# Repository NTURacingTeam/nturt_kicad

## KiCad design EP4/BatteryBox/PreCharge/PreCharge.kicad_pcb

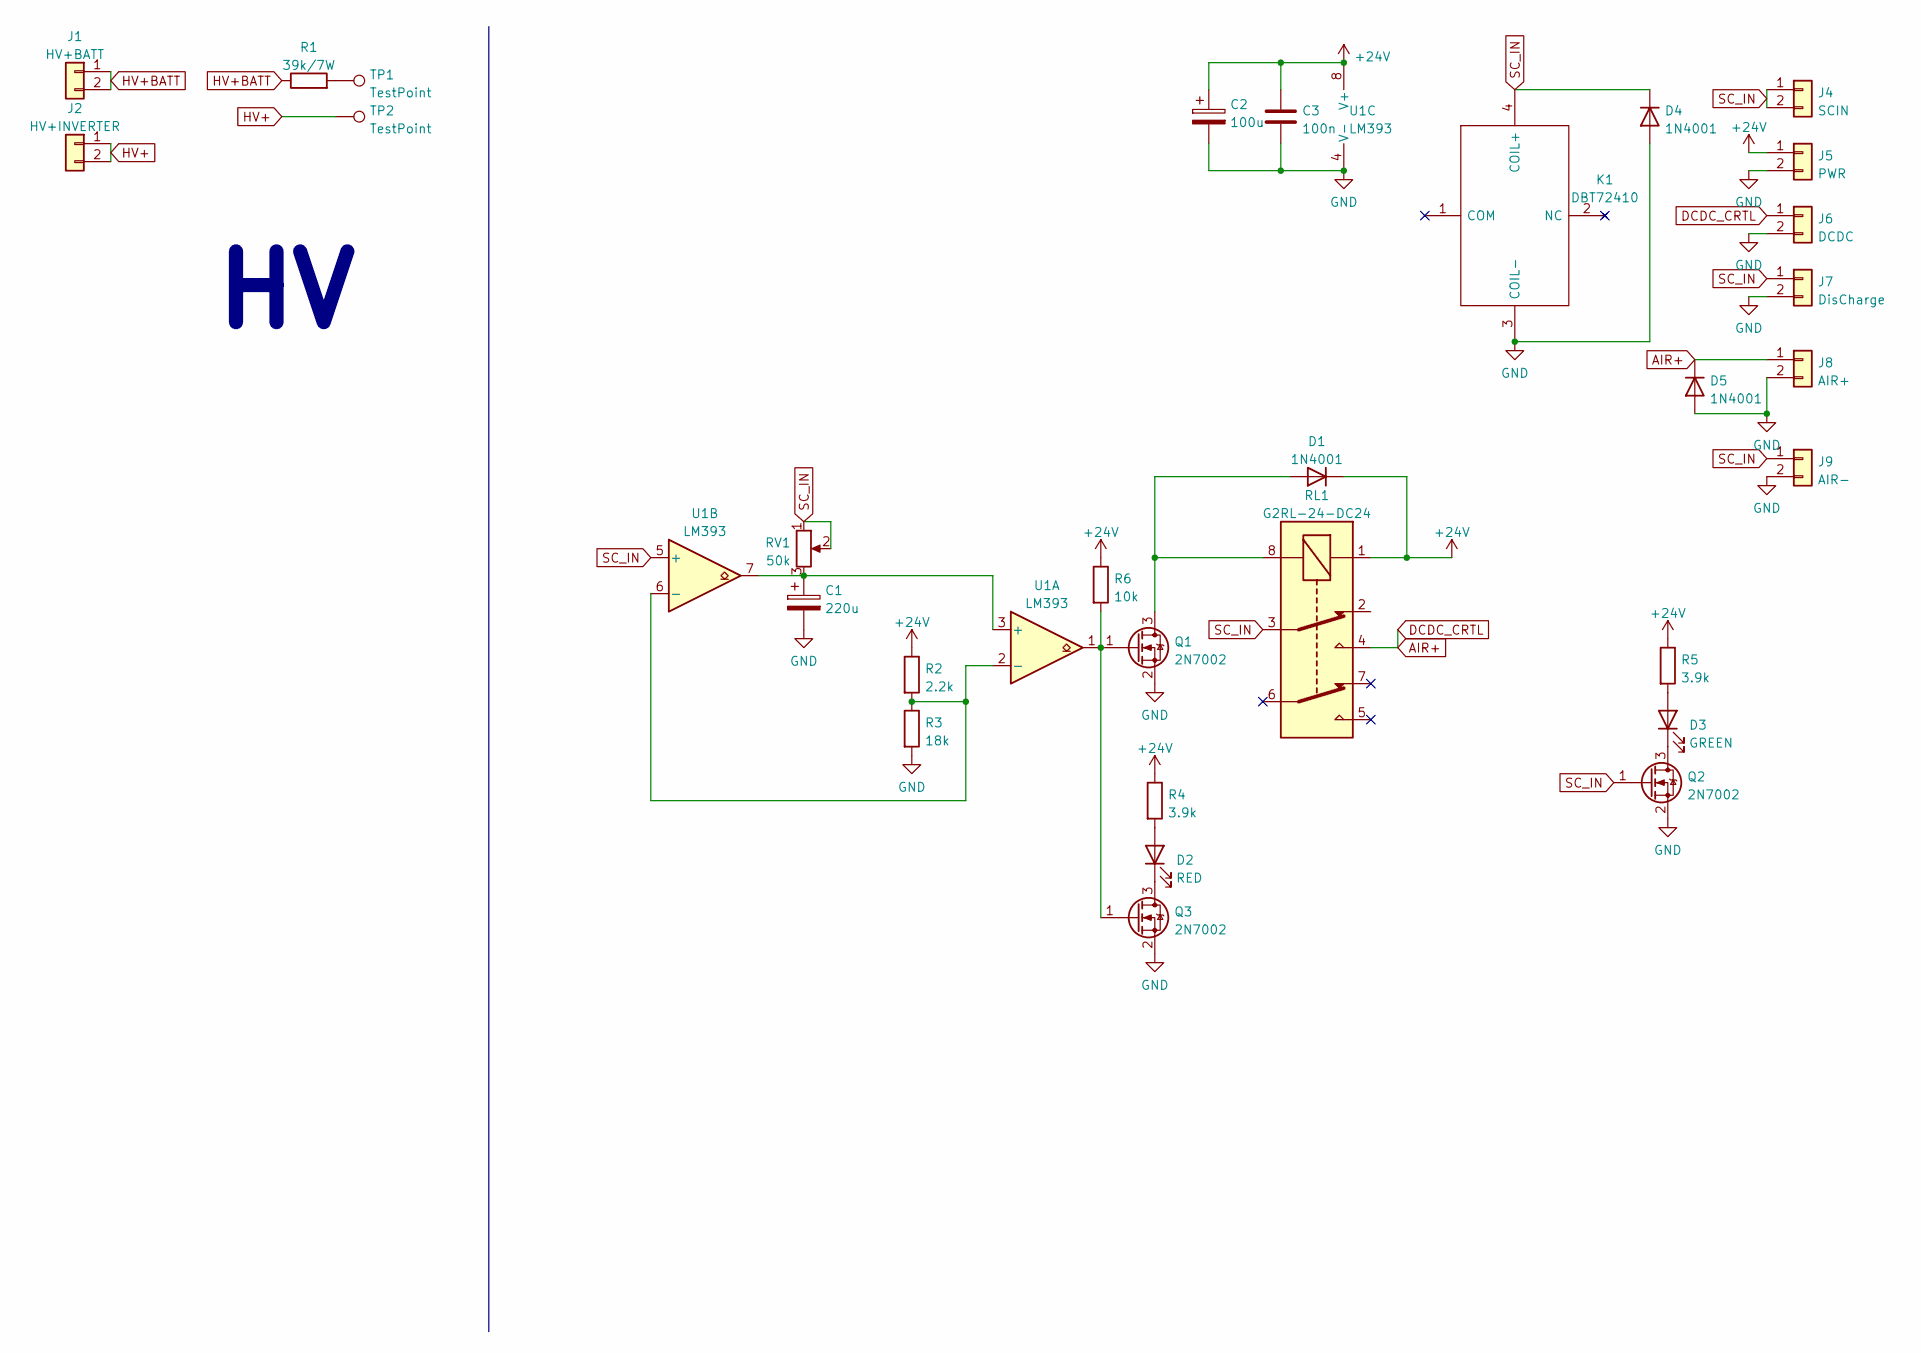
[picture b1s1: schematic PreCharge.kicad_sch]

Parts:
C1: 220u; CP_Elec_10x10
C2: 100u; CP_Elec_10x10
C3: 100n; C_0805_2012Metric_Pad1.18x1.45mm_HandSolder
D1, D4, D5: 1N4001; D_DO-41_SOD81_P10.16mm_Horizontal
D2: RED; LED_0805_2012Metric_Pad1.15x1.40mm_HandSolder
D3: GREEN; LED_0805_2012Metric_Pad1.15x1.40mm_HandSolder
J1: HV+BATT; DF33C2P33DSA24
J2: HV+INVERTER; DF33C2P33DSA24
J4: SCIN; DF33C2P33DSA24
J5: PWR; DF33C2P33DSA24
J6: DCDC; DF33C2P33DSA24
J7: DisCharge; DF33C2P33DSA24
J8: AIR+; DF33C2P33DSA24
J9: AIR-; DF33C2P33DSA24
K1: DBT72410; Manufacturer_Part_Number DBT72410
Q1, Q2, Q3: 2N7002; SOT-23
R1: 39k/7W; RESM24595X990N
R2: 2.2k; R_0805_2012Metric_Pad1.20x1.40mm_HandSolder
R3: 18k; R_0805_2012Metric_Pad1.20x1.40mm_HandSolder
R4, R5: 3.9k; R_0805_2012Metric_Pad1.20x1.40mm_HandSolder
R6: 10k; R_0805_2012Metric_Pad1.20x1.40mm_HandSolder
RL1: G2RL-24-DC24; Relay_DPDT_Omron_G2RL
RV1: 50k; Potentiometer_Bourns_3386P_Vertical
TP1, TP2: TestPoint; TestPoint_Loop_D2.50mm_Drill1.85mm
U1: LM393; SOIC-8_3.9x4.9mm_P1.27mm

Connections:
+24V: C2.1, C3.1, D1.1 (K), J5.1, R2.1, R4.1, R5.1, R6.1, RL1.1, U1.8 (V+)
AIR+: D5.1 (K), J6.1, J8.1, RL1.4
GND: C1.2, C2.2, C3.2, D4.2 (A), D5.2 (A), J5.2, J6.2, J7.2, J8.2, J9.2, K1.3 (COIL-), Q1.2 (S), Q2.2 (S), Q3.2 (S), R3.2, U1.4 (V-)
HV+: J2.1, J2.2, TP2.1
HV+BATT: J1.1, J1.2, R1.1
unnamed: D1.2 (A), Q1.3 (D), RL1.8
unnamed: D2.1 (K), Q3.3 (D)
unnamed: D2.2 (A), R4.2
unnamed: D3.1 (K), Q2.3 (D)
unnamed: D3.2 (A), R5.2
unnamed: Q1.1 (G), Q3.1 (G), R6.2, U1.1
unnamed: R1.2, TP1.1
unnamed: R2.2, R3.1, U1.2 (-), U1.6 (-)
unnamed: C1.1, RV1.3, U1.3 (+), U1.7
SC_IN: D4.1 (K), J4.1, J4.2, J7.1, J9.1, K1.4 (COIL+), Q2.1 (G), RL1.3, RV1.1, RV1.2, U1.5 (+)

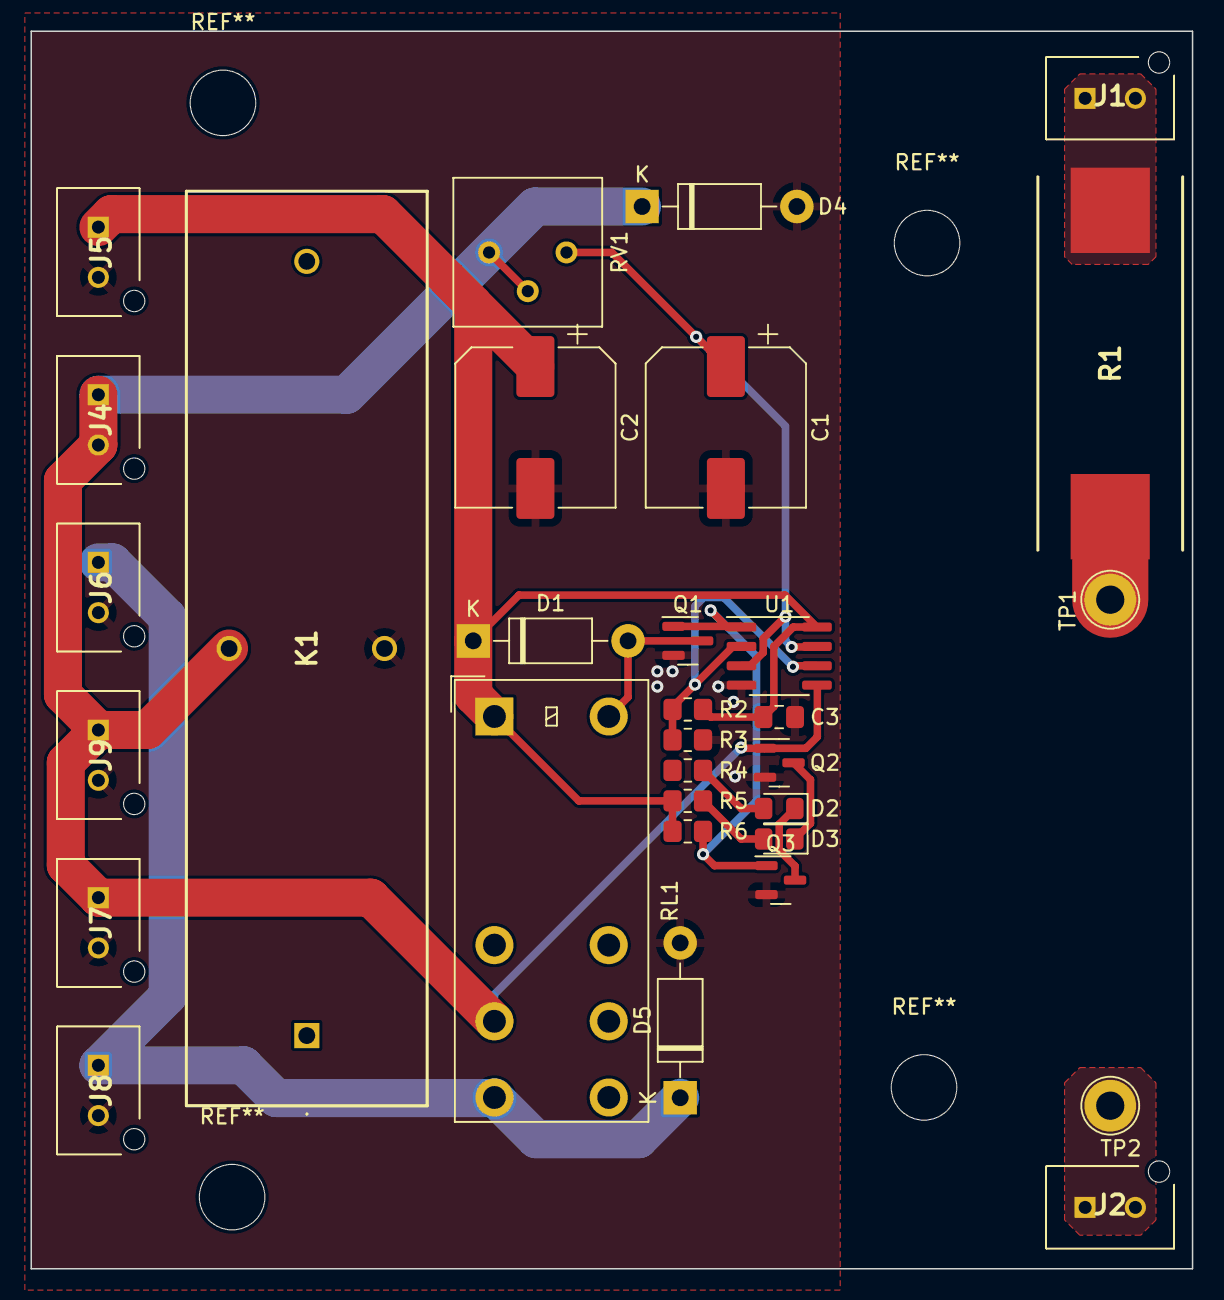
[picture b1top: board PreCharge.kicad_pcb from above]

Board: 2 copper layers, 76.2 x 81.2 mm, 31 parts (0 on the bottom side), 15 nets.

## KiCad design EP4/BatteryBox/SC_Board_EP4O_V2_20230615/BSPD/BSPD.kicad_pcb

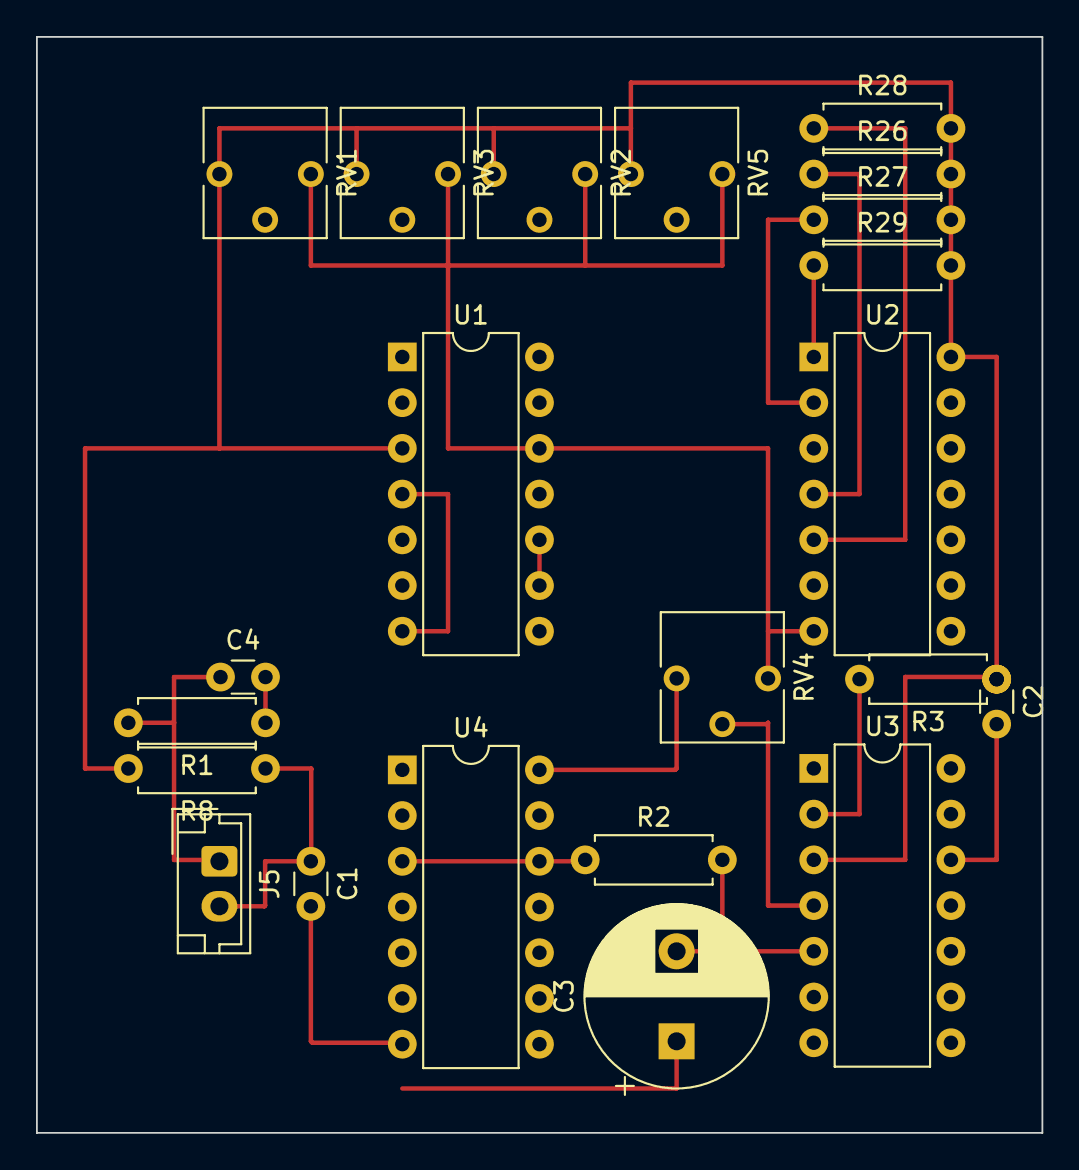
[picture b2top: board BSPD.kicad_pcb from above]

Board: 4 copper layers, 55.9 x 60.9 mm, 22 parts (0 on the bottom side), 18 nets.

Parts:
C1, C2, C4: 0.1uF; C_Disc_D3.0mm_W1.6mm_P2.50mm
C3: 100uF; CP_Radial_D10.0mm_P5.00mm
J5: BSPD I/O; JST_EH_B2B-EH-A_1x02_P2.50mm_Vertical
R1, R8, R26, R27, R28, R29: 1k; R_Axial_DIN0207_L6.3mm_D2.5mm_P7.62mm_Horizontal
R2: 5.1k; R_Axial_DIN0207_L6.3mm_D2.5mm_P7.62mm_Horizontal
R3: 39k; R_Axial_DIN0207_L6.3mm_D2.5mm_P7.62mm_Horizontal
RV1, RV2, RV3, RV4, RV5: R_POT; Potentiometer_Vishay_T73YP_Vertical
U1, U3: LM339; DIP-14_W7.62mm
U2: 74LS32; DIP-14_W7.62mm
U4: 74LS08; DIP-14_W7.62mm

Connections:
+5V: C2.1, R3.1, R8.2, R26.2, R27.2, R28.2, R29.2, RV1.1, RV2.1, RV3.1, RV4.1, RV5.1, U1.3 (V+), U2.14 (VCC), U3.3 (V+), U4.14 (VCC)
BPD_fault: R3.2, U3.2
GND: C1.2, C2.2, C3.1, C4.2, R1.1, RV1.3, RV2.3, RV3.3, RV4.3, RV5.3, U1.12 (V-), U2.7 (GND), U3.12 (V-), U4.7 (GND)
unnamed: C1.1, J5.2, R8.1, U1.4 (-), U1.7 (+)
unnamed: C3.2, R2.2, U3.5 (+)
unnamed: C4.1, J5.1, R1.2, U1.9 (+), U1.10 (-)
unnamed: R26.1, U1.13, U2.4
unnamed: R27.1, U1.1, U2.2
unnamed: R28.1, U1.14, U2.5
unnamed: R29.1, U1.2, U2.1
unnamed: RV1.2, U1.5 (+)
unnamed: RV2.2, U1.11 (+)
unnamed: RV3.2, U1.6 (-)
unnamed: RV4.2, U3.4 (-)
unnamed: RV5.2, U1.8 (-)
unnamed: U2.3, U4.1
unnamed: U2.6, U4.2
unnamed: R2.1, U4.3, U4.12

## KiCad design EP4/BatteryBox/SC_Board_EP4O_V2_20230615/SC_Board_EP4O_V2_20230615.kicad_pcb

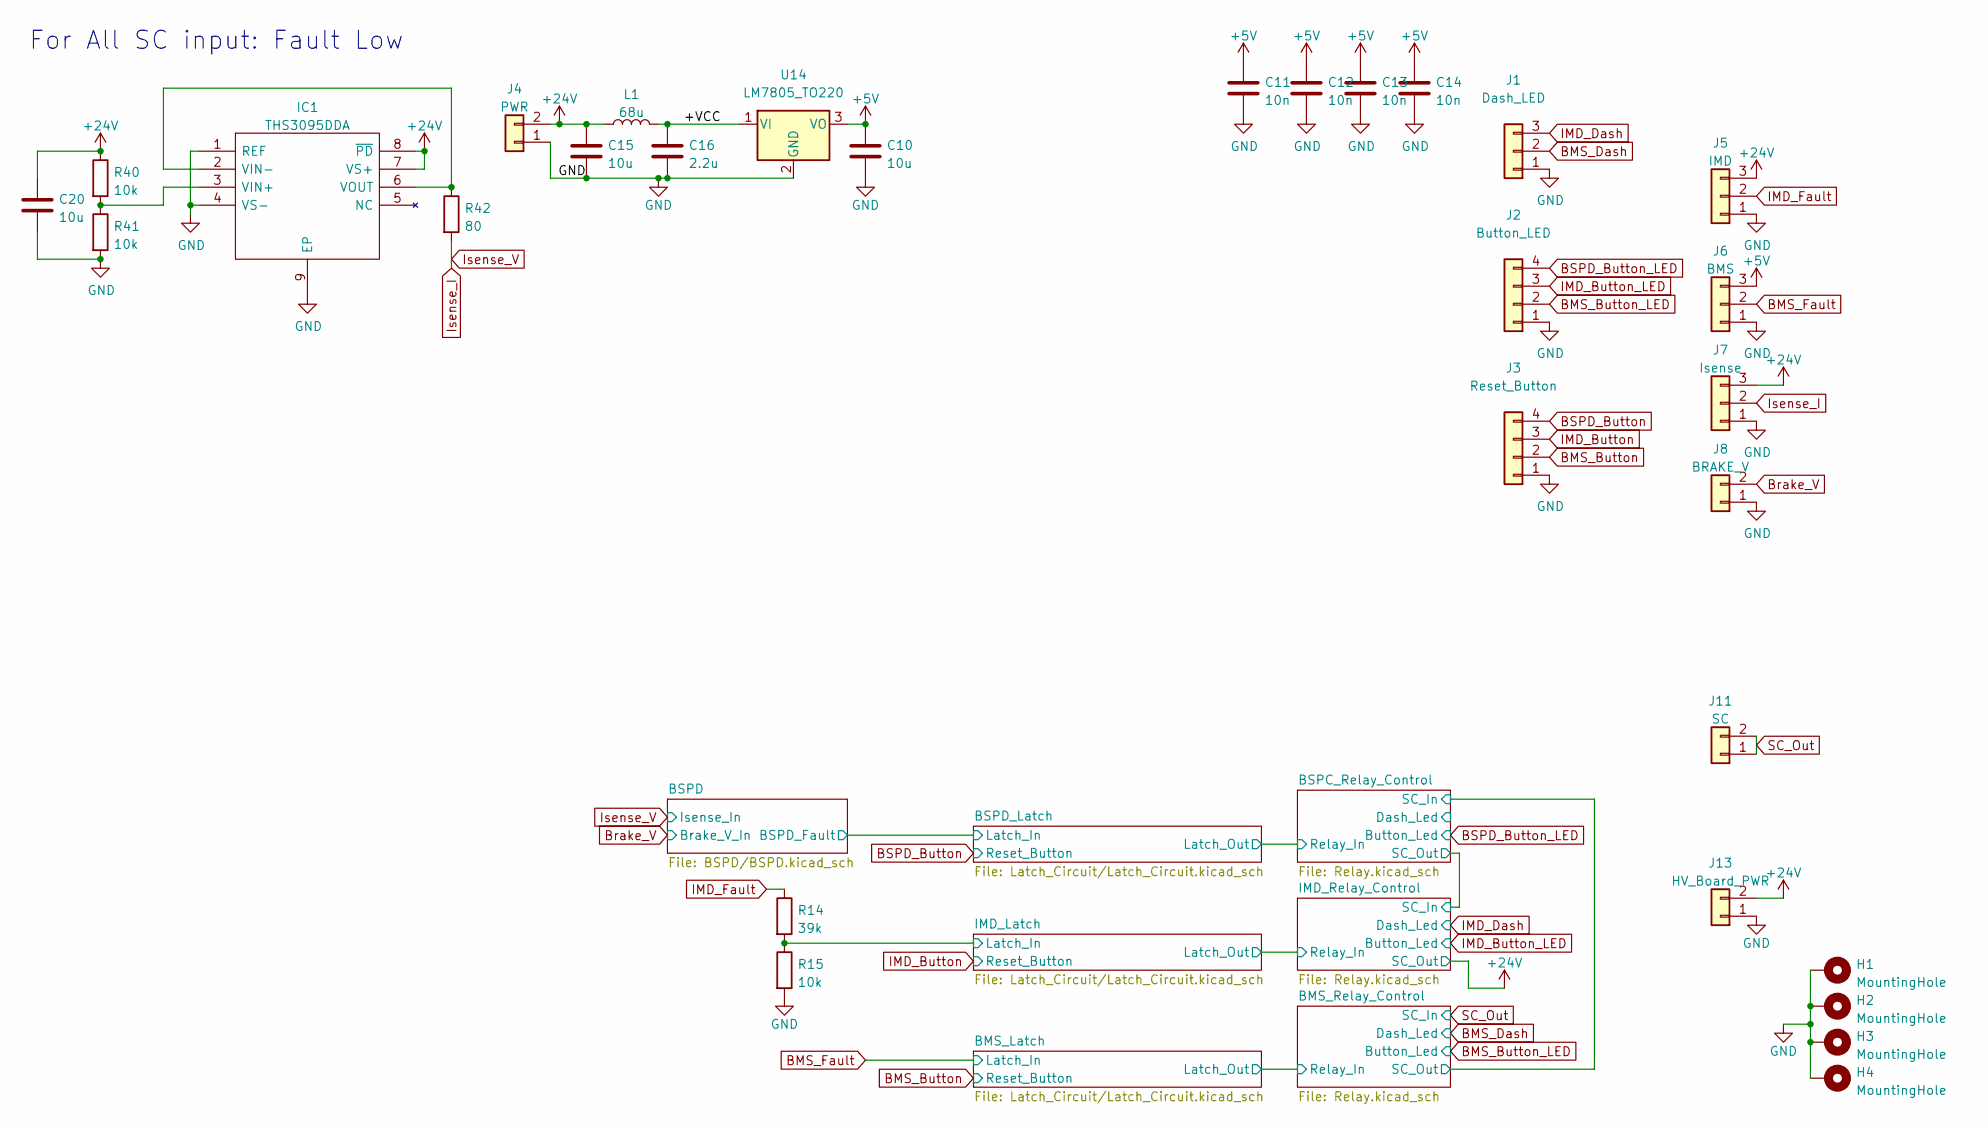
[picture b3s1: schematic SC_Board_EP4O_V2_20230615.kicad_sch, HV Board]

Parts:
C10, C15, C20: 10u; C_1206_3216Metric_Pad1.33x1.80mm_HandSolder
C11, C12, C13, C14: 10n; C_0805_2012Metric_Pad1.18x1.45mm_HandSolder
C16: 2.2u; C_1206_3216Metric_Pad1.33x1.80mm_HandSolder
H1, H2, H3, H4: MountingHole; MountingHole_4.3mm_M4_Pad_Via
IC1: THS3095DDA; SOIC127P600X170-9N; Mouser Part Number 595-THS3095DDA
J1: Dash_LED; JST_PH_B3B-PH-K_1x03_P2.00mm_Vertical
J2: Button_LED; JST_PH_B4B-PH-K_1x04_P2.00mm_Vertical
J3: Reset_Button; JST_PH_B4B-PH-K_1x04_P2.00mm_Vertical
J4: PWR; JST_PH_B2B-PH-K_1x02_P2.00mm_Vertical
J5: IMD; JST_PH_B3B-PH-K_1x03_P2.00mm_Vertical
J6: BMS; JST_PH_B3B-PH-K_1x03_P2.00mm_Vertical
J7: Isense; JST_PH_B3B-PH-K_1x03_P2.00mm_Vertical
J8: BRAKE_V; JST_PH_B2B-PH-K_1x02_P2.00mm_Vertical
J11: SC; JST_PH_B2B-PH-K_1x02_P2.00mm_Vertical
J13: HV_Board_PWR; JST_PH_B2B-PH-K_1x02_P2.00mm_Vertical
L1: 68u; RLS686
R14: 39k; R_0805_2012Metric_Pad1.20x1.40mm_HandSolder
R15, R40, R41: 10k; R_0805_2012Metric_Pad1.20x1.40mm_HandSolder
R42: 80; R_Axial_Power_L38.0mm_W6.4mm_P40.64mm
U14: LM7805_TO220; TO-220-3_Vertical

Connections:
+5V: C10.1, C11.1, C12.1, C13.1, C14.1, J6.3, U14.3 (VO); also elsewhere on the board
+24V: C15.1, C20.1, IC1.7 (VS+), IC1.8 (~PD), J4.2, J5.3, J7.3, J13.2, L1.1, R40.1; also elsewhere on the board
/+VCC: C16.1, L1.2, U14.1 (VI)
/IMD_Latch/Latch_In: R14.2, R15.1; also elsewhere on the board
BMS_Button: J3.2; also elsewhere on the board
BMS_Button_LED: J2.2; also elsewhere on the board
BMS_Dash: J1.2; also elsewhere on the board
BMS_Fault: J6.2; also elsewhere on the board
BSPD_Button: J3.4; also elsewhere on the board
BSPD_Button_LED: J2.4; also elsewhere on the board
Brake_V: J8.2; also elsewhere on the board
GND: C10.2, C11.2, C12.2, C13.2, C14.2, C15.2, C16.2, C20.2, H1.1, H2.1, H3.1, H4.1, IC1.1 (REF), IC1.4 (VS-), IC1.9 (EP), J1.1, J2.1, J3.1, J4.1, J5.1, J6.1, J7.1, J8.1, J13.1, R15.2, R41.2, U14.2 (GND); also elsewhere on the board
IMD_Button: J3.3; also elsewhere on the board
IMD_Button_LED: J2.3; also elsewhere on the board
IMD_Dash: J1.3; also elsewhere on the board
IMD_Fault: J5.2, R14.1
Isense_I: J7.2, R42.2; also elsewhere on the board
unnamed: IC1.2 (VIN-), IC1.6 (VOUT), R42.1
unnamed: IC1.3 (VIN+), R40.2, R41.1
SC_Out: J11.1, J11.2; also elsewhere on the board

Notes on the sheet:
For All SC input: Fault Low

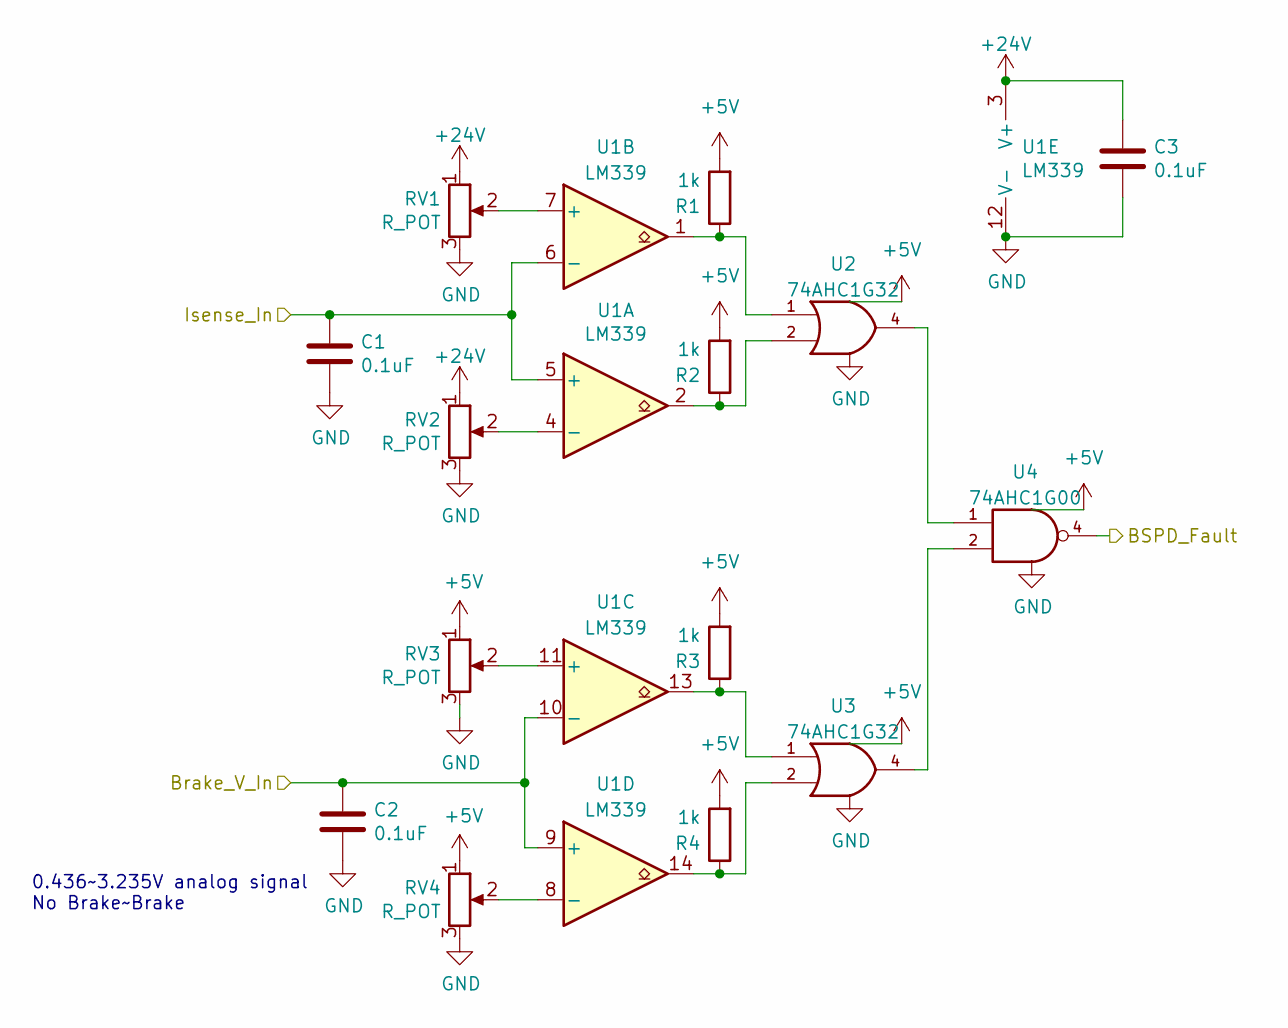
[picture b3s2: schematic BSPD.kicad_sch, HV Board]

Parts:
C1, C2, C3: 0.1uF; C_0805_2012Metric_Pad1.18x1.45mm_HandSolder
R1, R2, R3, R4: 1k; R_0805_2012Metric_Pad1.20x1.40mm_HandSolder
RV1, RV2, RV3, RV4: R_POT; Potentiometer_Bourns_3296P_Horizontal
U1: LM339; SOIC-14_3.9x8.7mm_P1.27mm
U2, U3: 74AHC1G32; SOT-23-5_HandSoldering
U4: 74AHC1G00; SOT-23-5_HandSoldering

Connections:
+5V: R1.2, R2.2, R3.2, R4.2, RV3.1, RV4.1, U2.5 (VCC), U3.5 (VCC), U4.5 (VCC); also elsewhere on the board
+24V: C3.1, RV1.1, RV2.1, U1.3 (V+); also elsewhere on the board
/BSPD/BSPD_Fault: U4.4; also elsewhere on the board
Brake_V: C2.1, U1.9 (+), U1.10 (-); also elsewhere on the board
GND: C1.2, C2.2, C3.2, RV1.3, RV2.3, RV3.3, RV4.3, U1.12 (V-), U2.3 (GND), U3.3 (GND), U4.3 (GND); also elsewhere on the board
Isense_I: C1.1, U1.5 (+), U1.6 (-); also elsewhere on the board
unnamed: R1.1, U1.1, U2.1
unnamed: R2.1, U1.2, U2.2
unnamed: R3.1, U1.13, U3.1
unnamed: R4.1, U1.14, U3.2
unnamed: RV1.2, U1.7 (+)
unnamed: RV2.2, U1.4 (-)
unnamed: RV3.2, U1.11 (+)
unnamed: RV4.2, U1.8 (-)
unnamed: U2.4, U4.1
unnamed: U3.4, U4.2

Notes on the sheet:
0.436~3.235V analog signal No Brake~Brake

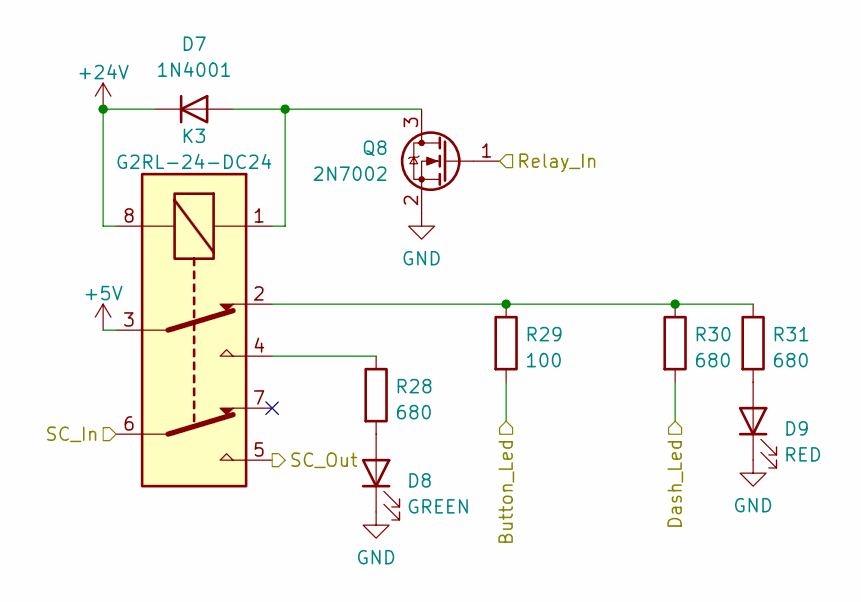
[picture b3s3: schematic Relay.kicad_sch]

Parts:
D7: 1N4001; D_MiniMELF_Handsoldering
D8: GREEN; D_0805_2012Metric_Pad1.15x1.40mm_HandSolder
D9: RED; D_0805_2012Metric_Pad1.15x1.40mm_HandSolder
K3: G2RL-24-DC24; Relay_DPDT_Omron_G2RL; Mouser Part Number 653-G2RL-24-DC5
Q8: 2N7002; SOT-23
R28, R30, R31: 680; R_0805_2012Metric_Pad1.20x1.40mm_HandSolder
R29: 100; R_0805_2012Metric_Pad1.20x1.40mm_HandSolder

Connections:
+5V: K3.3; also elsewhere on the board
+24V: D7.1 (K), K3.8; also elsewhere on the board
/BMS_Relay_Control/SC_Out: K3.6; also elsewhere on the board
/BSPC_Relay_Control/Dash_Led: R30.2
/BSPC_Relay_Control/Relay_In: Q8.1 (G); also elsewhere on the board
/BSPC_Relay_Control/SC_Out: K3.5; also elsewhere on the board
BSPD_Button_LED: R29.2; also elsewhere on the board
GND: D8.1 (K), D9.1 (K), Q8.2 (S); also elsewhere on the board
unnamed: D7.2 (A), K3.1, Q8.3 (D)
unnamed: D8.2 (A), R28.2
unnamed: D9.2 (A), R31.2
unnamed: K3.2, R29.1, R30.1, R31.1
unnamed: K3.4, R28.1

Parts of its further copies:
D10, D13: 1N4001; D_MiniMELF_Handsoldering
D11, D14: GREEN; D_0805_2012Metric_Pad1.15x1.40mm_HandSolder
D12, D15: RED; D_0805_2012Metric_Pad1.15x1.40mm_HandSolder
K4, K5: G2RL-24-DC24; Relay_DPDT_Omron_G2RL; Mouser Part Number 653-G2RL-24-DC5
Q9, Q10: 2N7002; SOT-23
R32, R34, R35, R36, R38, R39: 680; R_0805_2012Metric_Pad1.20x1.40mm_HandSolder
R33, R37: 100; R_0805_2012Metric_Pad1.20x1.40mm_HandSolder

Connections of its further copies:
+5V: K4.3, K5.3; also elsewhere on the board
+24V: D10.1 (K), D13.1 (K), K4.5, K4.8, K5.8; also elsewhere on the board
/BMS_Latch/Latch_Out: Q10.1 (G); also elsewhere on the board
/BMS_Relay_Control/SC_Out: K5.5; also elsewhere on the board
/BSPC_Relay_Control/SC_Out: K4.6; also elsewhere on the board
/IMD_Latch/Latch_Out: Q9.1 (G); also elsewhere on the board
BMS_Button_LED: R37.2; also elsewhere on the board
BMS_Dash: R38.2; also elsewhere on the board
GND: D11.1 (K), D12.1 (K), D14.1 (K), D15.1 (K), Q9.2 (S), Q10.2 (S); also elsewhere on the board
IMD_Button_LED: R33.2; also elsewhere on the board
IMD_Dash: R34.2; also elsewhere on the board
unnamed: D10.2 (A), K4.1, Q9.3 (D)
unnamed: D11.2 (A), R32.2
unnamed: D12.2 (A), R35.2
unnamed: D13.2 (A), K5.1, Q10.3 (D)
unnamed: D14.2 (A), R36.2
unnamed: D15.2 (A), R39.2
unnamed: K4.2, R33.1, R34.1, R35.1
unnamed: K4.4, R32.1
unnamed: K5.2, R37.1, R38.1, R39.1
unnamed: K5.4, R36.1
SC_Out: K5.6; also elsewhere on the board

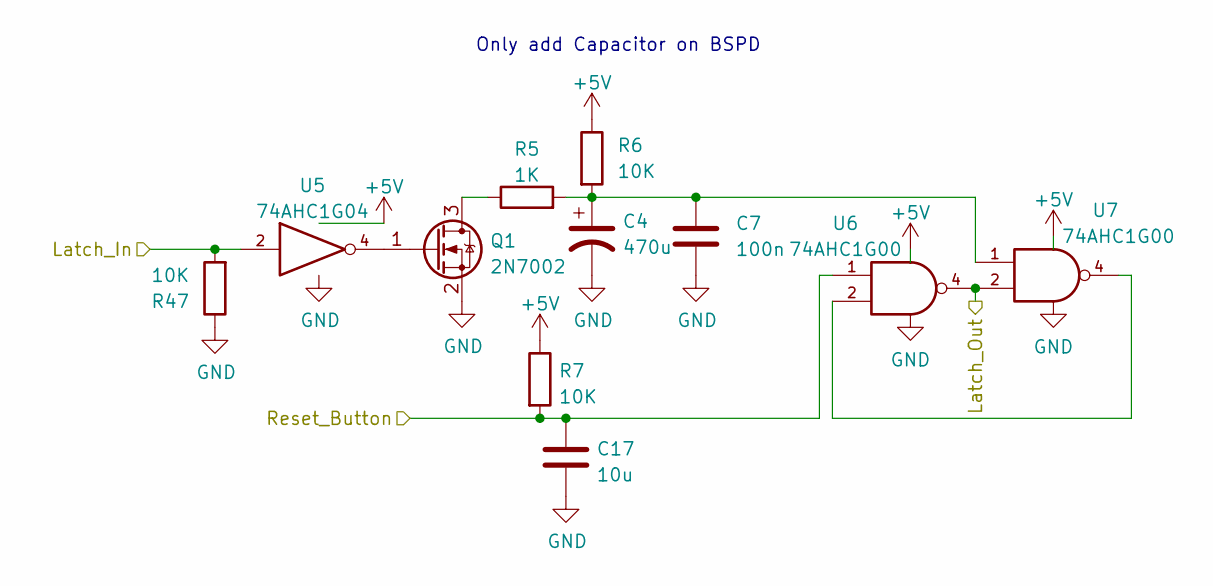
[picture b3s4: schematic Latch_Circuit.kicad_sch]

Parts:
C4: 470u; CP_Elec_10x10
C7: 100n; C_0805_2012Metric_Pad1.18x1.45mm_HandSolder
C17: 10u; C_1206_3216Metric_Pad1.33x1.80mm_HandSolder
Q1: 2N7002; SOT-23
R5: 1K; R_0805_2012Metric_Pad1.20x1.40mm_HandSolder
R6, R7, R47: 10K; R_0805_2012Metric_Pad1.20x1.40mm_HandSolder
U5: 74AHC1G04; SOT-23-5_HandSoldering
U6, U7: 74AHC1G00; SOT-23-5_HandSoldering

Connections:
+5V: R6.1, R7.1, U5.5 (VCC), U6.5 (VCC), U7.5 (VCC); also elsewhere on the board
/BSPC_Relay_Control/Relay_In: U6.4, U7.2; also elsewhere on the board
/BSPD/BSPD_Fault: R47.2, U5.2; also elsewhere on the board
BSPD_Button: C17.1, R7.2, U6.1; also elsewhere on the board
GND: C4.2, C7.2, C17.2, Q1.2 (S), R47.1, U5.3 (GND), U6.3 (GND), U7.3 (GND); also elsewhere on the board
unnamed: C4.1, C7.1, R5.2, R6.2, U7.1
unnamed: Q1.1 (G), U5.4
unnamed: Q1.3 (D), R5.1
unnamed: U6.2, U7.4

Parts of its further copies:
C5, C6: 470u; CP_Elec_10x10
C8, C9: 100n; C_0805_2012Metric_Pad1.18x1.45mm_HandSolder
C18, C19: 10u; C_1206_3216Metric_Pad1.33x1.80mm_HandSolder
Q2, Q3: 2N7002; SOT-23
R8, R11: 1K; R_0805_2012Metric_Pad1.20x1.40mm_HandSolder
R9, R10, R12, R13, R48, R49: 10K; R_0805_2012Metric_Pad1.20x1.40mm_HandSolder
U8, U11: 74AHC1G04; SOT-23-5_HandSoldering
U9, U10, U12, U13: 74AHC1G00; SOT-23-5_HandSoldering

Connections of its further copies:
+5V: R9.1, R10.1, R12.1, R13.1, U8.5 (VCC), U9.5 (VCC), U10.5 (VCC), U11.5 (VCC), U12.5 (VCC), U13.5 (VCC); also elsewhere on the board
/BMS_Latch/Latch_Out: U12.4, U13.2; also elsewhere on the board
/IMD_Latch/Latch_In: R48.2, U8.2; also elsewhere on the board
/IMD_Latch/Latch_Out: U9.4, U10.2; also elsewhere on the board
BMS_Button: C19.1, R13.2, U12.1; also elsewhere on the board
BMS_Fault: R49.2, U11.2; also elsewhere on the board
GND: C5.2, C6.2, C8.2, C9.2, C18.2, C19.2, Q2.2 (S), Q3.2 (S), R48.1, R49.1, U8.3 (GND), U9.3 (GND), U10.3 (GND), U11.3 (GND), U12.3 (GND), U13.3 (GND); also elsewhere on the board
IMD_Button: C18.1, R10.2, U9.1; also elsewhere on the board
unnamed: C5.1, C8.1, R8.2, R9.2, U10.1
unnamed: C6.1, C9.1, R11.2, R12.2, U13.1
unnamed: Q2.1 (G), U8.4
unnamed: Q2.3 (D), R8.1
unnamed: Q3.1 (G), U11.4
unnamed: Q3.3 (D), R11.1
unnamed: U9.2, U10.4
unnamed: U12.2, U13.4

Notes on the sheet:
Only add Capacitor on BSPD

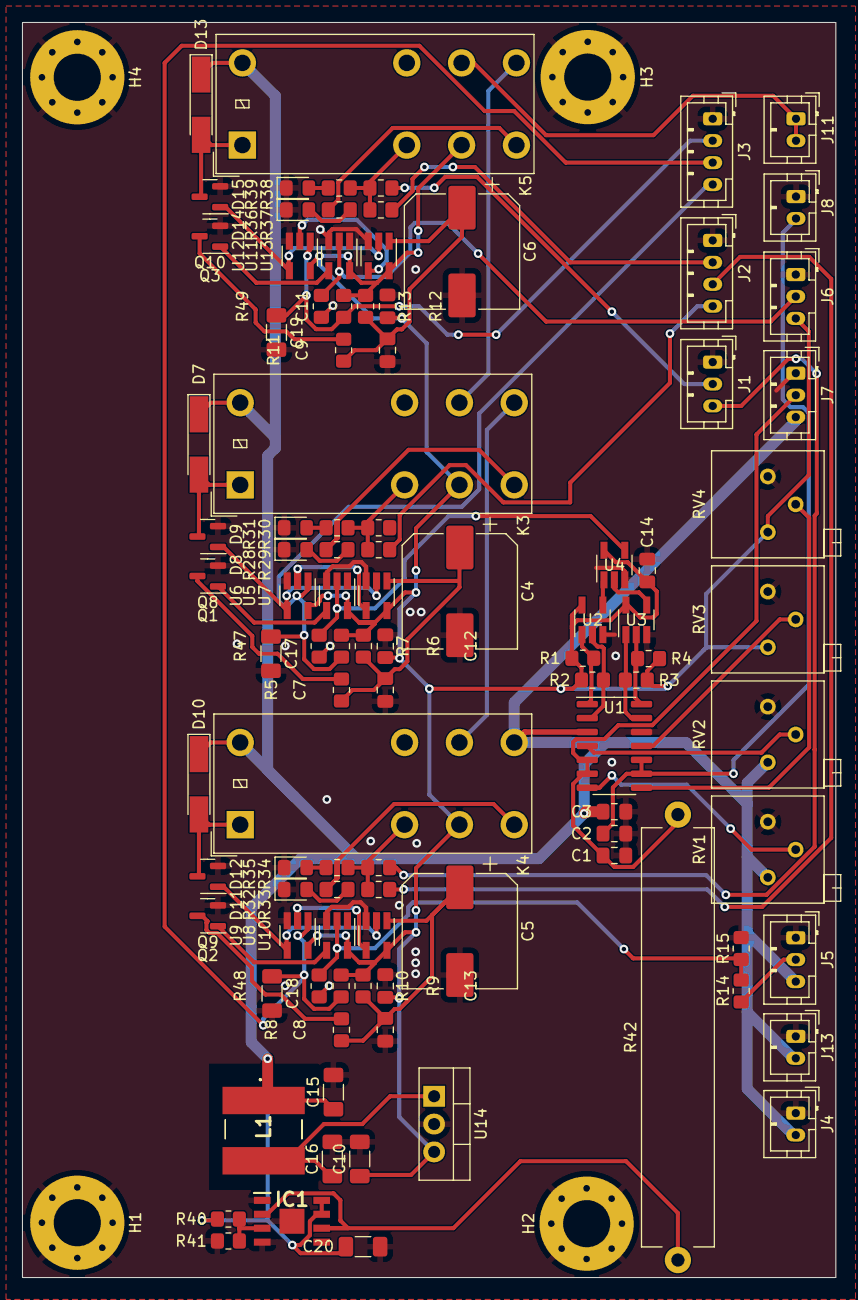
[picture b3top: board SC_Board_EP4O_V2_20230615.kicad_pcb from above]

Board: 2 copper layers, 74.2 x 114.5 mm, 105 parts (0 on the bottom side), 63 nets.

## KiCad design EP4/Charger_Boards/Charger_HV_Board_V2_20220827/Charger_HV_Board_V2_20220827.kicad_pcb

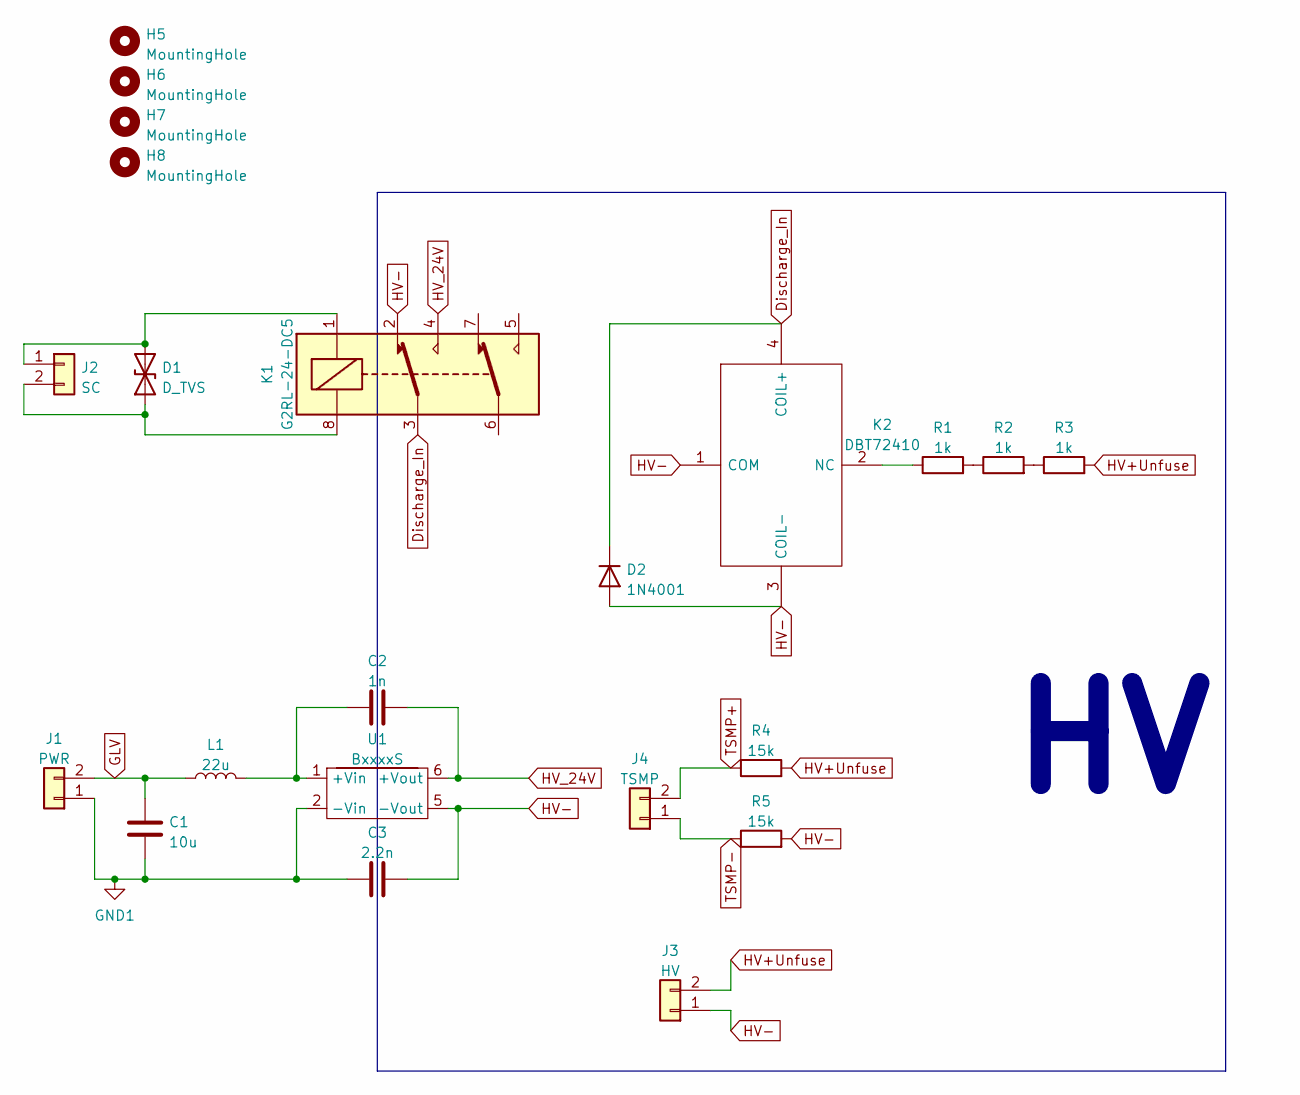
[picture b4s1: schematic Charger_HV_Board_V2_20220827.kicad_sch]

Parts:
C1: 10u; C_1206_3216Metric_Pad1.33x1.80mm_HandSolder
C2: 1n; C_Axial_L5.1mm_D3.1mm_P15.00mm_Horizontal
C3: 2.2n; C_Axial_L5.1mm_D3.1mm_P15.00mm_Horizontal
D1: D_TVS; D_DO-15_P15.24mm_Horizontal
D2: 1N4001; D_DO-41_SOD81_P10.16mm_Horizontal
H5, H6, H7, H8: MountingHole; MountingHole_4.3mm_M4
J1: PWR; JST_VH_B2P-VH-B_1x02_P3.96mm_Vertical
J2: SC; JST_VH_B2P-VH-B_1x02_P3.96mm_Vertical
J3: HV; TE_1747996
J4: TSMP; TE_1747996
K1: G2RL-24-DC5; Relay_DPDT_Omron_G2RL; Mouser Part Number 653-G2RL-24-DC5
K2: DBT72410; Manufacturer_Part_Number DBT72410
L1: 22u; RLS226R
R1, R2, R3: 1k; R_Axial_Power_L48.0mm_W12.5mm_P60.96mm
R4, R5: 15k; R_Axial_DIN0411_L9.9mm_D3.6mm_P20.32mm_Horizontal
U1: BxxxxS

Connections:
Discharge_In: D2.1 (K), K1.3, K2.4 (COIL+)
GLV: C1.1, J1.2, L1.1
GND: C1.2, C3.1, J1.1, U1.2 (-Vin)
HV+Unfuse: J3.2, R3.2, R4.2
HV-: C3.2, D2.2 (A), J3.1, K1.2, K2.1 (COM), K2.3 (COIL-), R5.2, U1.5 (-Vout)
HV_24V: C2.2, K1.4, U1.6 (+Vout)
unnamed: C2.1, L1.2, U1.1 (+Vin)
unnamed: D1.1 (A1), J2.2, K1.8
unnamed: D1.2 (A2), J2.1, K1.1
unnamed: K2.2 (NC), R1.1
unnamed: R1.2, R2.1
unnamed: R2.2, R3.1
TSMP+: J4.2, R4.1
TSMP-: J4.1, R5.1

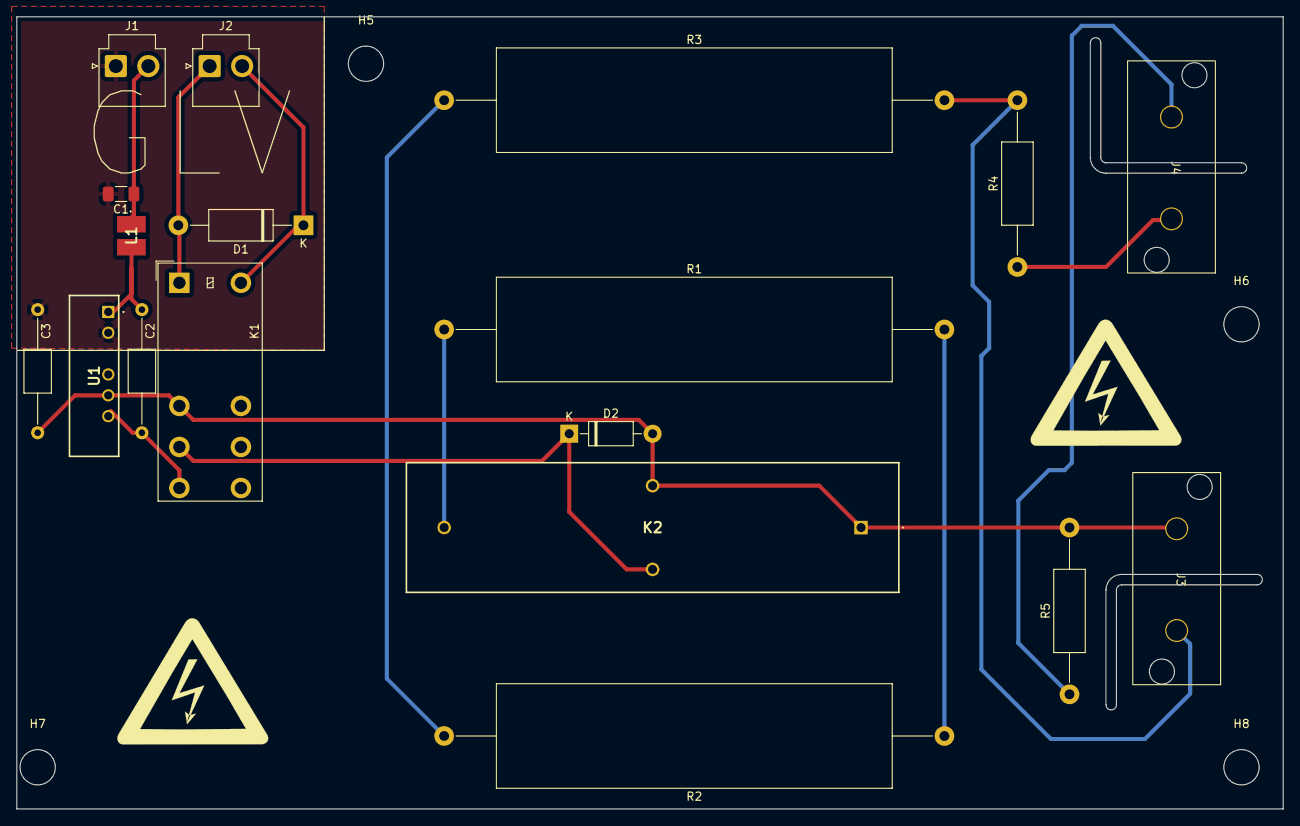
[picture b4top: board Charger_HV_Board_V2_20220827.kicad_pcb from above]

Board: 2 copper layers, 154.3 x 96.5 mm, 22 parts (0 on the bottom side), 14 nets.
